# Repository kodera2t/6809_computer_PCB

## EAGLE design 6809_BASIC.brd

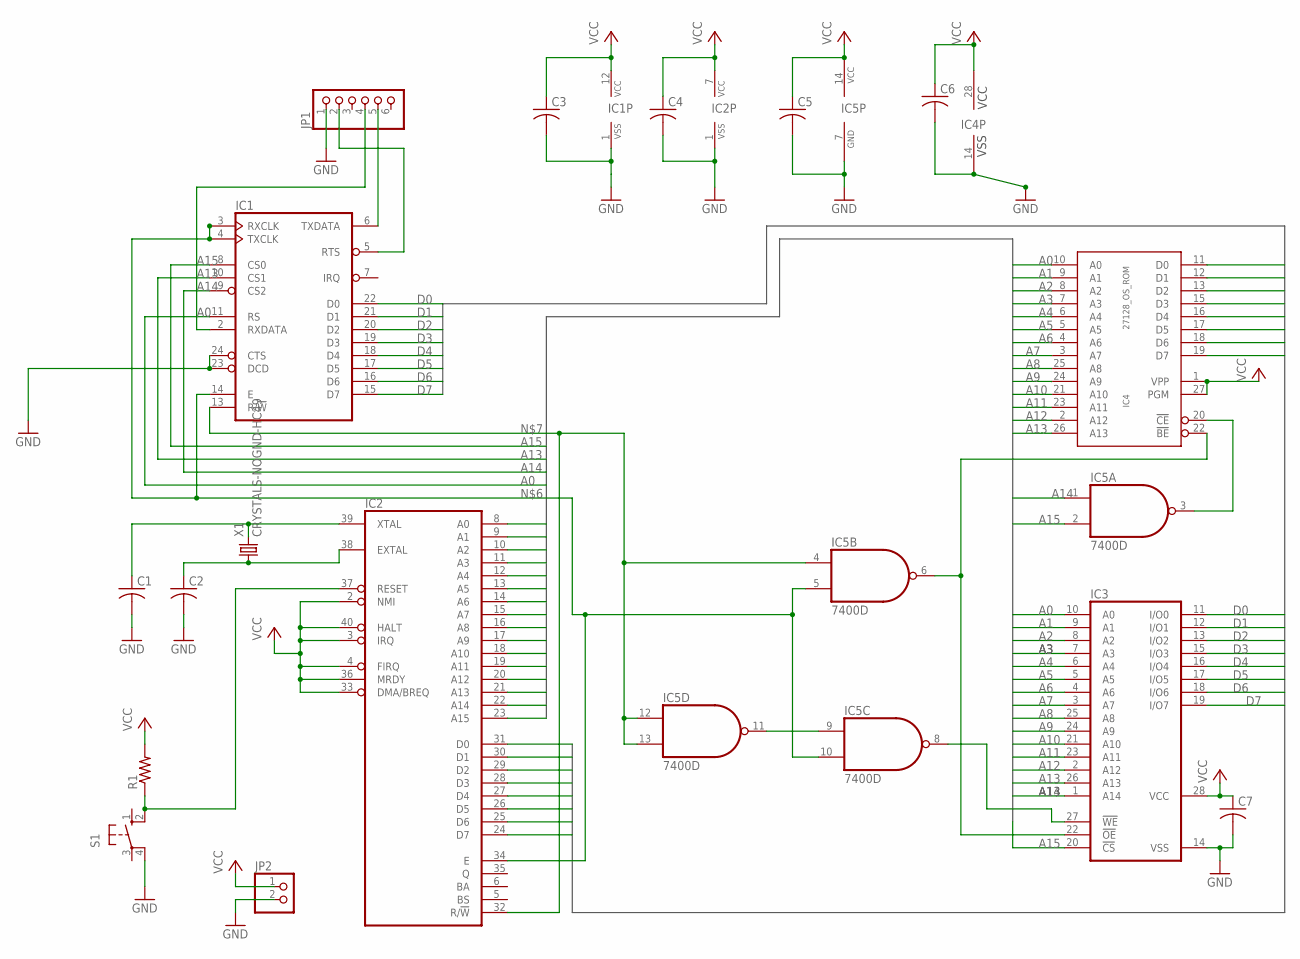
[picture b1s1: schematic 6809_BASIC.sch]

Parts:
C1, C2, C3, C4, C5, C6, C7: C-USC1608; C1608
IC1: 6850; DIL24
IC2: 6809; DIL40
IC3: 62256P; DIL28-6
IC4: 27128_OS_ROM; DIL28
IC5: 7400D; SO14
JP1: HEADER-1X6; 1X06_OVAL
JP2: HEADER-1X2; 1X02_OVAL
R1: R-US_R0603; R0603
S1: 10-XX; B3F-10XX
X1: CRYSTALS-NOGND-HC49; HC49

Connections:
A0: IC1.11 (RS), IC2.8 (A0), IC3.10 (A0), IC4.10 (A0)
A1: IC2.9 (A1), IC3.9 (A1), IC4.9 (A1)
A2: IC2.10 (A2), IC3.8 (A2), IC4.8 (A2)
A3: IC2.11 (A3), IC3.7 (A3), IC4.7 (A3)
A4: IC2.12 (A4), IC3.6 (A4), IC4.6 (A4)
A5: IC2.13 (A5), IC3.5 (A5), IC4.5 (A5)
A6: IC2.14 (A6), IC3.4 (A6), IC4.4 (A6)
A7: IC2.15 (A7), IC3.3 (A7), IC4.3 (A7)
A8: IC2.16 (A8), IC3.25 (A8), IC4.25 (A8)
A9: IC2.17 (A9), IC3.24 (A9), IC4.24 (A9)
A10: IC2.18 (A10), IC3.21 (A10), IC4.21 (A10)
A11: IC2.19 (A11), IC3.23 (A11), IC4.23 (A11)
A12: IC2.20 (A12), IC3.2 (A12), IC4.2 (A12)
A13: IC1.10 (CS1), IC2.21 (A13), IC3.26 (A13), IC4.26 (A13)
A14: IC1.9 (CS2), IC2.22 (A14), IC3.1 (A14), IC5.1 (I0)
A15: IC1.8 (CS0), IC2.23 (A15), IC3.20 (!CS), IC5.2 (I1)
D0: IC1.22 (D0), IC2.31 (D0), IC3.11 (I/O0), IC4.11 (D0)
D1: IC1.21 (D1), IC2.30 (D1), IC3.12 (I/O1), IC4.12 (D1)
D2: IC1.20 (D2), IC2.29 (D2), IC3.13 (I/O2), IC4.13 (D2)
D3: IC1.19 (D3), IC2.28 (D3), IC3.15 (I/O3), IC4.15 (D3)
D4: IC1.18 (D4), IC2.27 (D4), IC3.16 (I/O4), IC4.16 (D4)
D5: IC1.17 (D5), IC2.26 (D5), IC3.17 (I/O5), IC4.17 (D5)
D6: IC1.16 (D6), IC2.25 (D6), IC3.18 (I/O6), IC4.18 (D6)
D7: IC1.15 (D7), IC2.24 (D7), IC3.19 (I/O7), IC4.19 (D7)
GND: C1.2, C2.2, C3.2, C4.2, C5.2, C6.2, C7.2, IC1.1 (VSS), IC1.23 (DCD), IC1.24 (CTS), IC2.1 (VSS), IC3.14 (VSS), IC4.14 (VSS), IC5.7 (GND), JP1.1, JP2.2, S1.4 (P1)
unnamed: IC3.27 (!WE), IC5.8 (O)
unnamed: IC3.22 (!OE), IC4.22 (!BE), IC5.6 (O)
unnamed: IC5.9 (I0), IC5.11 (O)
unnamed: IC4.20 (!CE), IC5.3 (O)
unnamed: IC1.3 (RXCLK), IC1.4 (TXCLK), IC1.14 (E), IC2.34 (E), IC5.5 (I1), IC5.10 (I1)
unnamed: IC1.13 (R/!W), IC2.32 (R/!W), IC5.4 (I0), IC5.12 (I0), IC5.13 (I1)
unnamed: C2.1, IC2.38 (EXTAL), X1.1
unnamed: C1.1, IC2.39 (XTAL), X1.2
unnamed: IC2.37 (RESET), R1.1, S1.2 (S1)
unnamed: IC1.6 (TXDATA), JP1.5
unnamed: IC1.2 (RXDATA), JP1.4
unnamed: IC1.5 (RTS), JP1.2
VCC: C3.1, C4.1, C5.1, C6.1, C7.1, IC1.12 (VCC), IC2.2 (NMI), IC2.3 (IRQ), IC2.4 (FIRQ), IC2.7 (VCC), IC2.33 (DMA/BREQ), IC2.36 (MRDY), IC2.40 (HALT), IC3.28 (VCC), IC4.1 (VPP), IC4.27 (PGM), IC4.28 (VCC), IC5.14 (VCC), JP2.1, R1.2

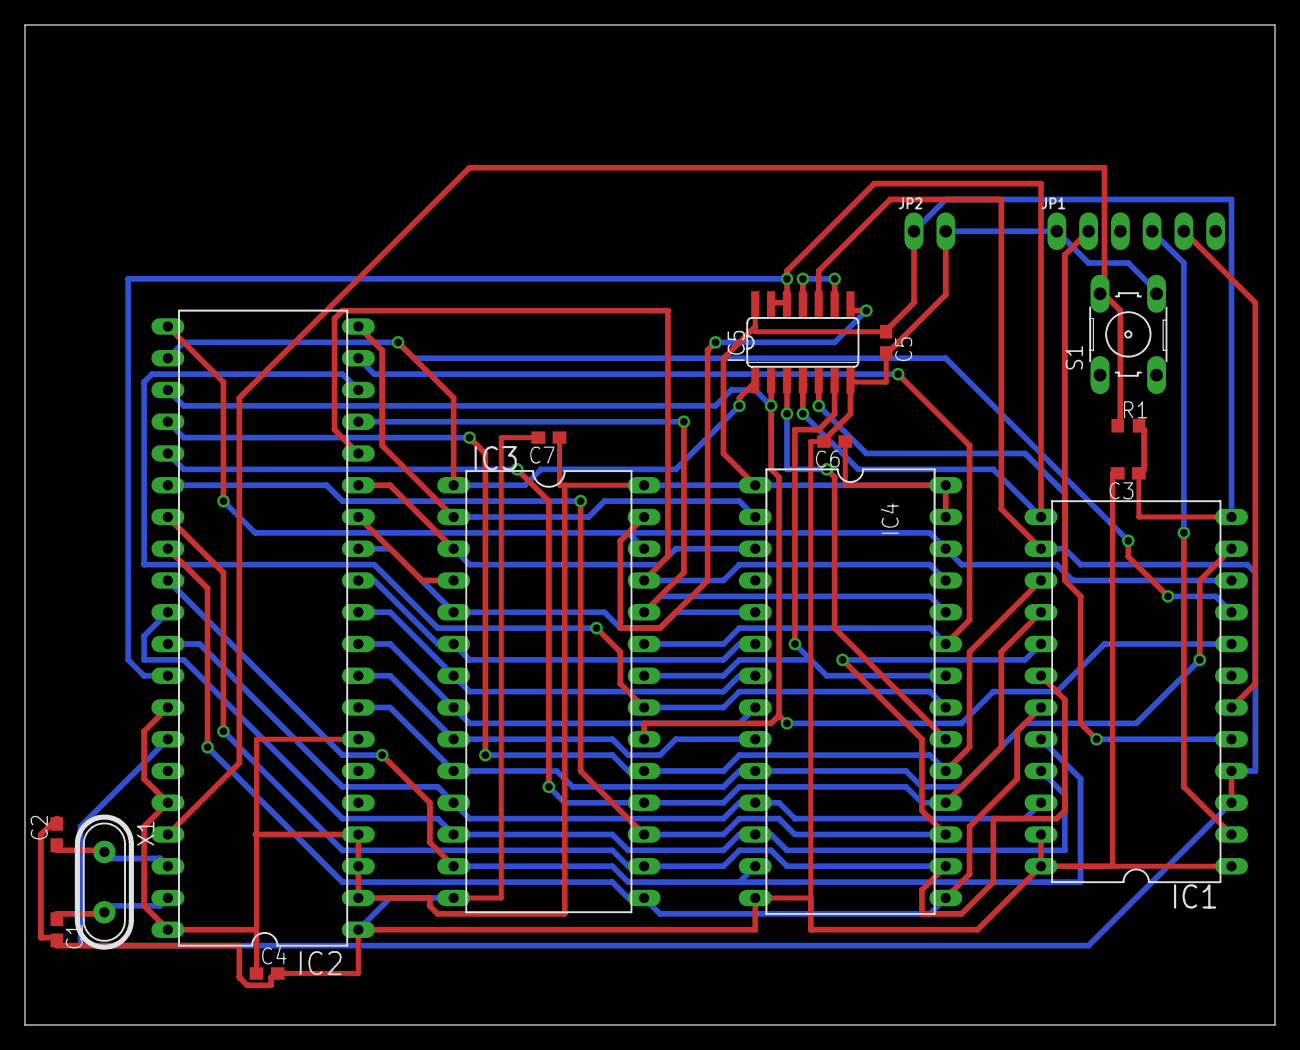
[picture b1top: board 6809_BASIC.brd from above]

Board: 2 copper layers, 100.0 x 80.0 mm, 17 parts (0 on the bottom side), 38 nets.

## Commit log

2015-11-21 initial submission

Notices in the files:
parts and their libraries:
eagle-6.5.0-atari: Copyright (c) 2010
Copyright (c) 2009
This library is licensed under the
Creative Commons Attribution 3.0 United States License.
OLED_mod: This work is placed in the public domain, and may be freely used for commercial and non-commercial work with the following conditions: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
